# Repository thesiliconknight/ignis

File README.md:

# Ignis
A low-voltage controller board for driving a 220V 400W aluminum PTC heater via an external SSR, it has a NTC for temperature readings, an OLED status/info display, and MOSFET-isolated relay stuff. The board uses the CH32V006F8P6 MCU, its mainly used for triggering the SSR and reading temps,it keeps all mains voltage completely off of the board.
## Pictures
| Top View | Bottom View |
| :---: | :---: |
|  |  |
## Features
* **Main Controller:** CH32V006F8P6,62KB Flash and 8KB RAM.
* **USB-C Power:** Board is powered over USB-C.
* **No High Voltage:** The PCB handles 5V/3.3V logic. The 220V AC mains load is kept off-board and switched safely via a external SSR.
* **Precision Sensing:** It uses a 100K NTC thermistor it can read up to 300°C.
* **OLED Interface:** I2C header for a 0.91" SSD1306 OLED displaying target temps, current temp, and heating status.
* **Status LEDs:** Inbuilt HEATING and RDY LEDs gives the heater state without needing a screen.
* **Button Header:** 5-pin header breaking out 4 tactile buttons for menu navigation.
## Components Used
* **Microcontroller:** WCH CH32V006F8P6 (TSSOP-20)
* **Power Input:** USB-C receptacle (power-only)
* **High Voltage Switch:** External SSR connected via terminal block
* **Heater:** 220V 400W PTC Aluminum Heating Plate
* **Thermistor:** 100K NTC connected via a JST-PH 2-pin connector
* **Screen:** 0.91" SSD1306 I2C OLED Module
* **Miscellaneous:** AMS1117-3.3V Regulator, AO3400A MOSFET, 4x tactile buttons, 2x status LEDs, and assorted 0603 passives.

## Bill of Materials (BOM)

| Qty | Component | Footprint | Designator(s) | Purchase Link | Price (Rs) |
| :---: | :--- | :--- | :--- | :--- | :--- |
| 1 | Conn_01x05_Socket (Buttons Header) | PinHeader_1x05_P2.54mm_Vertical | BTNS | N/A (any 2.54) | 0 (Already have) |
| 5 | 100nF Capacitor | C_0603_1608Metric | C1, C7, C8, C9, C4| [Link](https://www.google.com/aclk?sa=L&ai=DChsSEwjWubzfq_KWAxVioWwJHVqjE8wYACICCAEQExoCc2Y&co=1&gclid=CjwKCAjw2aPVBhBkEiwA0CpttxyZiuBTF60ARCzRlQv1wOvQn9Ln7Phh8AjBaM22zXAcPF-IAOMuhRoCiZ0QAvD_BwE&cid=CAAS9gHkaA9Mi-UPaGql0S6myvb2LanWs_hoczlRaLo8LdECcTfFA-W8eqSXpiu2Puml42bIa7v_HBw9_mI6NEkx9i0myCsUGftX24P3-UCmkTGwZrFsU0BwJ8dCOHYs8yvsxjpRQwjH_uvNDexOgG1wUDAQ0P-BJZl5-3Fow6dQR72VKUfztoA_-oSahlbYac6cqUK1pDvFReuEzmJMf88bpsotwaCjw0tTJoldDmuYUl_IsLorsIGnkdDTMLrtQRREB7B4yb7gziSToLH-9Onh54hlrXd5ChQYjjWFkbAuXQqNCxhsV-wsj35o-l13hoZH_t-N_gCMRv8&cce=2&sig=AOD64_08o8edncOKI5-4DwoIfZhybAqDPQ&ctype=5&q=&ved=2ahUKEwiRtrffq_KWAxWikuEIHdGiJzYQ5bgDKAB6BAgNEAs&adurl=) | 0 (Already have) |
| 1 | 1µF Capacitor | C_0603_1608Metric | C2 | [Link](https://robu.in/product/1uf-1000nf-50v-capacitor-0603-smd-package-pack-of-20/?gad_source=1&gad_campaignid=17427802703&gclid=CjwKCAjw2aPVBhBkEiwA0Cptt-klC8yW7VcnOm1oQzstlq8__qPEDX5lBedVzGTdGvl9aioaYdJKhBoCE5oQAvD_BwE) | 11.00 |
| 1 | 10µF Capacitor | C_0603_1608Metric | C5 | [Link](https://robu.in/product/cl10a106ma8nrnc-samsang-25v-10uf-x5r-%C2%B120-0603-multilayer-ceramic-capacitors-mlcc-smd-smt-rohs/?gad_source=1&gad_campaignid=20387462343&gclid=CjwKCAjw2aPVBhBkEiwA0Cptt_jrdtTLjbGVqE7j4SUPV9jsXRgV3px3erPD96kSMqSafKEsVnAZuRoCdTsQAvD_BwE) | 20.00 |
| 2 | LED (Heating / Ready) | LED_0805_2012Metric | HEATING, RDY | N/A (any 0805) | 0 (Already have) |
| 1 | USB-C Receptacle (Power Only) | USB4125-xx-x 6P TopMnt Horizontal | J6 | [Link](https://www.ktron.in/product/6-pin-usb-type-c-connector-smd/?srsltid=AU7gw4WCxG2g2oUNClt9s5qOYEoZTqFwBmndH3bq_uDZghMpFEObVLpm) | 15.00 |
| 1 | Conn_01x02_Socket (NTC) | JST_PH_S2B-PH-K_1x02_P2.00mm_Horizontal | NTC | [Link](https://robu.in/product/ph-aw-2mm-2-pin-wafer-male-connector-through-hole-right-angle/?gad_source=1&gad_campaignid=17427802703&gclid=CjwKCAjw2aPVBhBkEiwA0Cpttx-oBttgFg3lpMmzYvOTe5D44ZijZ2riTrUj3DSICNVzOlxnziOd7xoCIt0QAvD_BwE) | 0 (Already have) |
| 1 | JST-PH 2.0 Female Connector | N/A (Off-board wire harness) | — | [Link](https://hubtronics.in/1508?srsltid=AU7gw4Wmjln1E9tSbj1yLX3e6CGLNVZjP4-da3Qo7EFz9MvRA4VvwUHm) | 5.00 |
| 1 | Conn_01x03_Pin (Programming Header) | PinHeader_1x03_P2.54mm_Vertical | PRGRM | N/A (any 2.54) | 0 (Already have) |
| 1 | AO3400A N-Channel MOSFET | SOT-23 | Q1 | [Link](https://robu.in/product/ao3400-xblw-30v-5-8a-34m%cf%894-5v5a-1-4w-700mv250ua-1-n-channel-sot-23-3l-mosfets-rohs/) | 18.00 |
| 2 | 5.1kΩ Resistor | R_0603_1608Metric | R3, R9 | [Link](https://www.etstore.in/products/g7551?variant=46786456977659&country=IN&currency=INR&utm_medium=product_sync&utm_source=google&utm_content=sag_organic&utm_campaign=sag_organic&srsltid=AfmBOooAEYspNoTwyRh231GTfDzfoce41MVHsCR0qa07n6oFZs1zyCXtE4U) | 0 (Already have) |
| 1 | 1kΩ Resistor | R_0603_1608Metric | R4 | [Link](https://robu.in/product/1k-ohm-1-4w-0603-surface-mount-chip-resistor-pack-of-100/) | 10.15 |
| 1 | 10kΩ Resistor | R_0603_1608Metric | R5 | [Link](https://robu.in/product/10k-ohm-1-4w-0603-surface-mount-chip-resistor-pack-of-100/?gad_source=1&gad_campaignid=17427802703&gclid=CjwKCAjw2aPVBhBkEiwA0Cptt4oDgB-X0LF9_Wo0jAhzlSL1k49oGO2g-5uIWDAJX2wKff-w9ob-aRoCJvsQAvD_BwE) | 13.00 |
| 1 | 100kΩ Resistor | R_0603_1608Metric | R6 | [Link](https://robu.in/product/100k-ohm-1-4w-0603-surface-mount-chip-resistor-pack-of-100/) | 11.10 |
| 2 | 330Ω Resistor | R_0603_1608Metric | R7, R8 | [Link](https://robu.in/product/rc0603jr-07330rl-yageo-res-thick-film-0603-330-ohm-5-0-1w1-10w-%C2%B1100ppm-c-pad-smd-t-r/?gad_source=1&gad_campaignid=20387462343&gclid=CjwKCAjw2aPVBhBkEiwA0CpttxWKAhasnzZd6GH-hOIGY6Q7Vlr9g6yXAz9JQC7wOcykbgjOqbGy6BoCL8UQAvD_BwE) | 0 (Already have) |
| 1 | 0.91" I2C OLED | Untitled | SCREEN | [Link](https://www.ktron.in/product/0-91-inch-white-color-oled-display-i2c/) | 180.00 |
| 1 | Conn_01x02_Socket (SSR) | TerminalBlock_Phoenix_PT-1,5-2-5.0-H_1x02_P5.00mm_Horizontal | SSR | [Link](https://evelta.com/2-pin-screw-connectors-pcb/?sku=083-Prime-500-2&srsltid=AfmBOooWSOmGwzVSIBziLjGkH-_o1UC5T2c_B3cS1R9dAHhOMnPMw2FzNgQ) | 18.00 |
| 4 | SW_Push (6mm Tactile) | SW_PUSH_6mm | SW1, SW2, SW3, SW4 | [Link](https://robu.in/product/tsd001b06035a03-bzcn-6mm-6mm-50ma-round-button-direct-insert-6mm-350gf-12v-plugin-tactile-switches-rohs/?gad_source=1&gad_campaignid=17416544847&gclid=CjwKCAjw2aPVBhBkEiwA0CpttwqAopAQNE0Bei_-rT2XhkkkH0R7y_S-IDi2DNaC8Dg6daAmqfU6hhoCHdEQAvD_BwE) | 8.00 |
| 1 | CH32V006FxPx MCU | TSSOP-20_4.4x6.5mm_P0.65mm | U1 | [Link](https://www.etstore.in/products/a2668?_pos=1&_psq=ch32v006&_psid=08be7c9a0&_ss=e) | 40.00 |
| 1 | AMS1117-3.3 LDO | SOT-223-3_TabPin2 | U3 | [Link](https://robu.in/product/ams1117-3-3v-1a-sot-223-voltage-regulator-ic-pack-of-5-ics/?gad_source=1&gad_campaignid=17427802703&gclid=CjwKCAjw2aPVBhBkEiwA0Cpttz9w6ddF1XQumYWw6zxxuAcBU4UH7sDdK9DN8iZBH2cauwtZlcoLIxoCt08QAvD_BwE) | 18.00 |
| 1 | 220V 400W PTC Aluminum Heater Plate | N/A (Off-board) | — | [Link](https://hubtronics.in/aluminum-ptc-heating-plate?srsltid=AfmBOoofmvJnxpgYjjD9DPgNBhnGSLNf_ZdR-ngu1UgQvsgmx_wYjow5) | 500.00 |
| 1 | SSR-40 DA Solid State Relay | N/A (Off-board) | — | [Link](https://robu.in/product/dc-ac-ssr-40da-solid-state-relay-module-3-32vdc24-380vac-40a/?gad_source=1&gad_campaignid=17427802703&gclid=CjwKCAjw2aPVBhBkEiwA0Cptt2UdfUGUIJVYDIimHF9UJncTepMdDUKAhNORn_AaWNtUh0izbvHMLhoCZlQQAvD_BwE) | 269.00 |
| 1 | 100K NTC 3950 Thermistor | N/A (Off-board) | — | [Link](https://robu.in/product/thermistor-100k-ntc-1-meter-cable-temperature-sensor/?gad_source=1&gad_campaignid=17427803012&gclid=CjwKCAjw2aPVBhBkEiwA0Cptt76Yj44bFy054WNXM6b__TI9zpSi9M1uR_w4w8og-iXCbKlJB2rq0hoCktkQAvD_BwE) | 42.00 |
| | | | | **Component Total:** | **1178.25 Rs** (12.30$)|

*Note: Shipping and delivery fees across various vendors will add an estimated 100 - 200 Rs to the final cost.*

| Schematic Design |
| :---: |
|  |

| PCB Top Layer Routing | PCB Bottom Layer Routing |
| :---: | :---: |
|  |  |
### Connections
* **Power (USB-C to 3.3V):** 5V via USB-C (J6) and routes to the SSR connector and the AMS1117 V.REG (U3), which powers the MCU, OLED, and thermistor etc.
* **Thermistor Input (NTC):** Connects the 100K NTC between 3.3V and the MCU's ADC pin (PD2).
* **SSR Driver (SSR):** The MCU's PWM pin (PC3) switches the AO3400 Gate (Q1). The MOSFET pulls the negative side of the SSR terminal to GND, triggering the external relay.
* **OLED Header (SCREEN):** Connected to PC1 (SDA) and PC2 (SCK).
* **Button Header (BTNS):** 5-pin header breaking out the 4 tactile switches (SW1–SW4).
* **Programming Header (PRGRM):** Breaks out 3.3V, GND, and the single-wire debug line (PD1 / SWIO) for the programmer.
* **Status LEDs:** HEATING and RDY LEDs (Pin PD2 & PD3)
## License
This hardware project is open-source and licensed under the CERN Open Hardware Licence Version 2 - Strongly Reciprocal (CERN-OHL-S-2.0). 
You are free to copy, modify, distribute, and manufacture this board for personal or commercial use. However, if you modify these schematic or layout files and distribute your new design, you must release those modifications under this exact same CERN-OHL-S-2.0 license.
This design is shared without any warranty or implied guarantee. Check the LICENSE file for the full legal text.

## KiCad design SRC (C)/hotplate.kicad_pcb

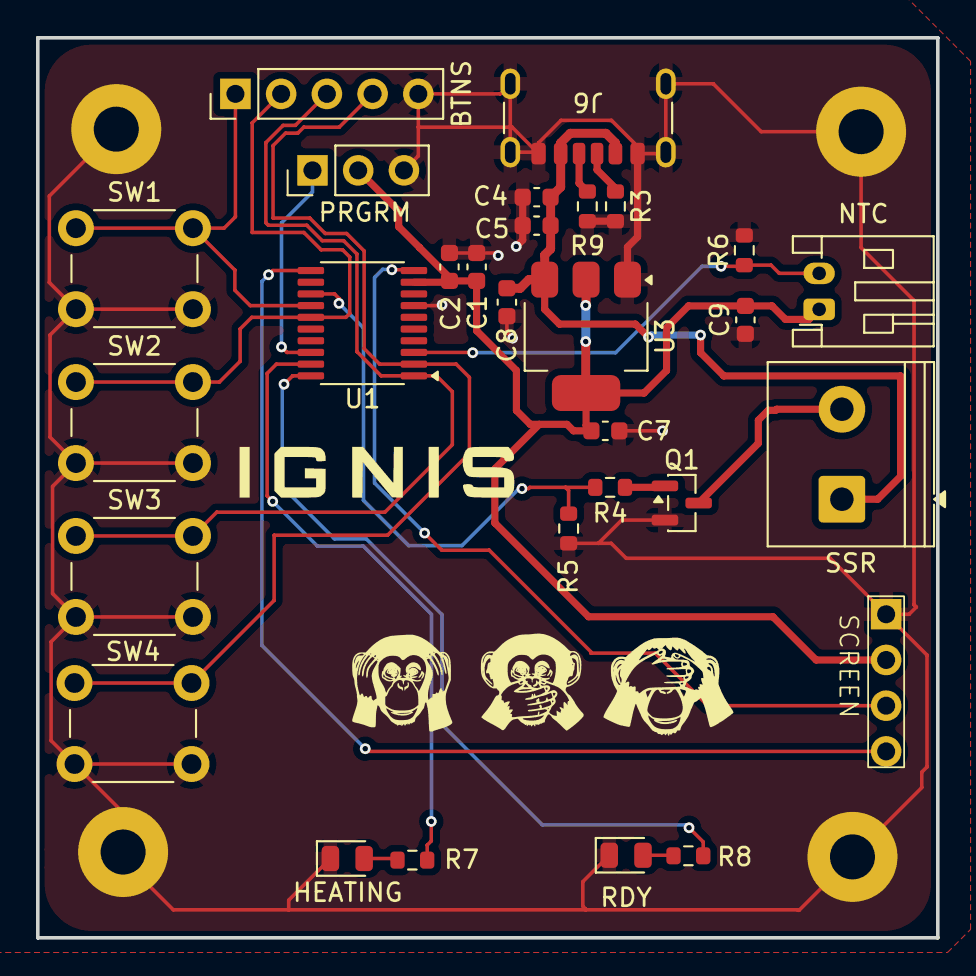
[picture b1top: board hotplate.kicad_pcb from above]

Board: 2 copper layers, 50.0 x 50.0 mm, 33 parts (0 on the bottom side), 20 nets.

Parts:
BTNS: Conn_01x05_Socket; PinHeader_1x05_P2.54mm_Vertical
C1, C7, C8, C9: 100nF; C_0603_1608Metric
C2: 1uF; C_0603_1608Metric
C4: 0.1 uF; C_0603_1608Metric
C5: 10uF; C_0603_1608Metric
H1, H2, H3, H4: MountingHole_Pad; MountingHole_2.5mm_Pad
HEATING: LED; LED_0805_2012Metric
J6: USB_C_Receptacle_PowerOnly_6P; USB_C_Receptacle_GCT_USB4125-xx-x_6P_TopMnt_Horizontal
NTC: Conn_01x02_Socket; JST_PH_S2B-PH-K_1x02_P2.00mm_Horizontal
PRGRM: Conn_01x03_Pin; PinHeader_1x03_P2.54mm_Vertical
Q1: AO3400A; SOT-23
R3, R9: 5.1k; R_0603_1608Metric
R4: 1k; R_0603_1608Metric
R5: 10k; R_0603_1608Metric
R6: 100K; R_0603_1608Metric
R7, R8: 330; R_0603_1608Metric
RDY: LED; LED_0805_2012Metric
SCREEN: 0.91_OLED; Untitled
SSR: Conn_01x02_Socket; TerminalBlock_Phoenix_PT-1,5-2-5.0-H_1x02_P5.00mm_Horizontal
SW1, SW2, SW3, SW4: SW_Push; SW_PUSH_6mm
U1: CH32V006FxPx; TSSOP-20_4.4x6.5mm_P0.65mm
U3: AMS1117-3.3; SOT-223-3_TabPin2

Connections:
+3.3V: C1.2, C2.2, C7.1, C9.2, NTC.1, PRGRM.2, SCREEN.2 (VCC), U1.9 (VDD), U3.2 (VO)
/C_P_2: Q1.3 (D), SSR.2
/PC0: SCREEN.3 (SCK), U1.10 (PC0)
/PC1: SCREEN.4 (SDA), U1.11 (PC1)
/PC3: R4.2, R5.2, U1.13 (PC3)
/PC4: BTNS.1, SW1.1, U1.14 (PC4)
/PC5: BTNS.2, SW2.1, U1.15 (PC5)
/PD2: R7.1, U1.19 (PD2)
/PD3: R8.1, U1.20 (PD3)
/PD4: BTNS.3, SW3.1, U1.1 (PD4)
/PD5: BTNS.4, SW4.1, U1.2 (PD5)
/PD6: NTC.2, R6.1, U1.3 (PD6)
/SWIO: PRGRM.1, U1.18 (PD1)
GND: BTNS.5, C1.1, C2.1, C4.1, C5.1, C7.2, C8.2, C9.1, H1.1 (1_1), H2.1 (1_1), H3.1 (1_1), H4.1 (1_1), HEATING.1 (K), J6.A12 (GND), J6.B12 (GND), J6.SH (SHIELD), PRGRM.3, Q1.2 (S), R3.2, R5.1, R6.2, R9.2, RDY.1 (K), SCREEN.1 (GND), SW1.2, SW2.2, SW3.2, SW4.2, U1.7 (VSS), U3.1 (GND)
unnamed: HEATING.2 (A), R7.2
unnamed: R8.2, RDY.2 (A)
unnamed: J6.A5 (CC1), R3.1
unnamed: J6.B5 (CC2), R9.1
unnamed: Q1.1 (G), R4.1
VBUS: C4.2, C5.2, C8.1, J6.A9 (VBUS), J6.B9 (VBUS), SSR.1, U3.3 (VI)

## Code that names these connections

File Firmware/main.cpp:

#include <Wire.h>
#include <Adafruit_GFX.h>
#include <Adafruit_SSD1306.h>

// pins
#define RELAY PC3  
#define NTC_PIN PD2
#define R_LED PA1
#define G_LED PA2
#define B_START PD4
#define B_UP PC5
#define B_DN PC4

float setpt = 220.0; 
float t_now = 0.0;
bool active = false; 
bool firing = false;

Adafruit_SSD1306 oled(128, 32, &Wire, -1);

void setup() {
  pinMode(RELAY, OUTPUT);
  pinMode(R_LED, OUTPUT);
  pinMode(G_LED, OUTPUT);
  
  // internal pullups for the tact switches
  pinMode(B_START, INPUT_PULLUP);
  pinMode(B_UP, INPUT_PULLUP);
  pinMode(B_DN, INPUT_PULLUP);
  
  digitalWrite(RELAY, LOW);
  digitalWrite(R_LED, LOW);
  digitalWrite(G_LED, LOW);

  Wire.begin();
  if(!oled.begin(SSD1306_SWITCHCAPVCC, 0x3C)) {
    while(true); // stuck here if screen is dead
  }
  
  oled.clearDisplay();
  oled.setTextSize(1);
  oled.setTextColor(SSD1306_WHITE);
  oled.setCursor(0, 10);
  oled.print("waking up...");
  oled.display();
  delay(1000);
}

void loop() {
  // hacky debounce lol
  if (!digitalRead(B_START)) {
    active = !active;
    delay(300); 
  }
  if (!digitalRead(B_UP)) {
    setpt += 5.0;
    delay(150);
  }
  if (!digitalRead(B_DN)) {
    setpt -= 5.0;
    delay(150);
  }

  int raw_adc = analogRead(NTC_PIN);
  
  // if thermistor unplugs it reads max/min usually
  if (raw_adc == 0 || raw_adc > 4090) {
    digitalWrite(RELAY, LOW);
    active = false;
    oled.clearDisplay();
    oled.setCursor(0,0);
    oled.print("ERR: SENSOR DED");
    oled.display();
    delay(500);
    return; 
  }

  // steinhart hart magic math
  float res = 100000.0 / ((4095.0 / (float)raw_adc) - 1.0);
  float kelvin = log(res / 100000.0);
  kelvin /= 3950.0;
  kelvin += 1.0 / (25.0 + 273.15);
  t_now = (1.0 / kelvin) - 273.15;

  // relay logic
  if (active) {
    if (t_now < (setpt - 2.0)) {
      digitalWrite(RELAY, HIGH);
      firing = true;
    } else if (t_now >= setpt) {
      digitalWrite(RELAY, LOW);
      firing = false;
    }
  } else {
    digitalWrite(RELAY, LOW);
    firing = false;
  }

  // blinkies
  if (active && firing) {
    digitalWrite(R_LED, HIGH);
    digitalWrite(G_LED, LOW);
  } else if (active && !firing) {
    digitalWrite(R_LED, LOW);
    digitalWrite(G_LED, HIGH);
  } else {
    digitalWrite(R_LED, LOW);
    digitalWrite(G_LED, LOW);
  }

  // draw screen stuff
  oled.clearDisplay();
  oled.setTextSize(1);
  oled.setCursor(0, 0);
  oled.print("Tgt:");
  oled.print(setpt, 0);
  
  oled.setCursor(80, 0);
  if(active) {
    oled.print(firing ? "HOT" : "OK");
  } else {
    oled.print("OFF");
  }

  oled.setTextSize(2);
  oled.setCursor(20, 15);
  oled.print(t_now, 1);
  oled.print("C");
  oled.display();
  
  delay(50); // don't freeze
}
